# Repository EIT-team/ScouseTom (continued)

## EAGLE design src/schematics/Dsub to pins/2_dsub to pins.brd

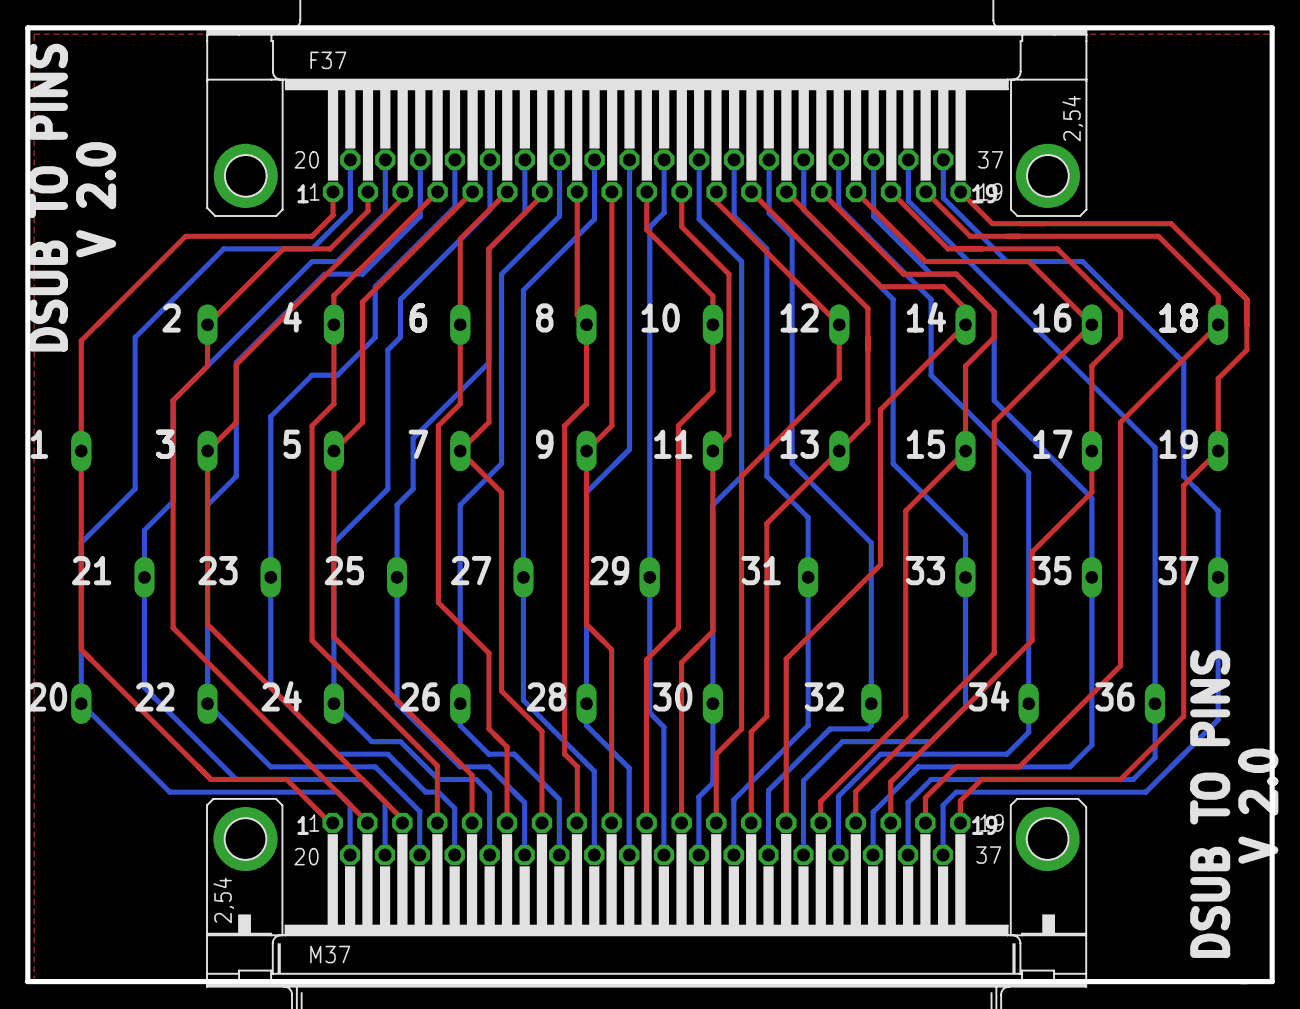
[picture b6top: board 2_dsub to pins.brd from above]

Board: 2 copper layers, 98.5 x 75.5 mm, 39 parts (0 on the bottom side), 37 nets.

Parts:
X1, X2, X3, X4, X5, X6, X7, X8, X9, X10, X11, X12, X13, X14, X15, X16, X17, X18, X19, X20, X21, X22, X23, X24, X25, X26, X27, X28, X29, X30, X31, X32, X33, X34, X35, X36, X37: 22-23-2021
X40: M37HP
X41: F37HP

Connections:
1: X1.1, X40.1, X41.1
2: X2.1, X40.2, X41.2
3: X3.1, X40.3, X41.3
4: X4.1, X40.4, X41.4
5: X5.1, X40.5, X41.5
6: X6.1, X40.6, X41.6
7: X7.1, X40.7, X41.7
8: X8.1, X40.8, X41.8
9: X9.1, X40.9, X41.9
10: X10.1, X40.10, X41.10
11: X11.1, X40.11, X41.11
12: X12.1, X40.12, X41.12
13: X13.1, X40.13, X41.13
14: X14.1, X40.14, X41.14
15: X15.1, X40.15, X41.15
16: X16.1, X40.16, X41.16
17: X17.1, X40.17, X41.17
18: X18.1, X40.18, X41.18
19: X19.1, X40.19, X41.19
20: X20.1, X40.20, X41.20
21: X21.1, X40.21, X41.21
22: X22.1, X40.22, X41.22
23: X23.1, X40.23, X41.23
24: X24.1, X40.24, X41.24
25: X25.1, X40.25, X41.25
26: X26.1, X40.26, X41.26
27: X27.1, X40.27, X41.27
28: X28.1, X40.28, X41.28
29: X29.1, X40.29, X41.29
30: X30.1, X40.30, X41.30
31: X31.1, X40.31, X41.31
32: X32.1, X40.32, X41.32
33: X33.1, X40.33, X41.33
34: X34.1, X40.34, X41.34
35: X35.1, X40.35, X41.35
36: X36.1, X40.36, X41.36
37: X37.1, X40.37, X41.37

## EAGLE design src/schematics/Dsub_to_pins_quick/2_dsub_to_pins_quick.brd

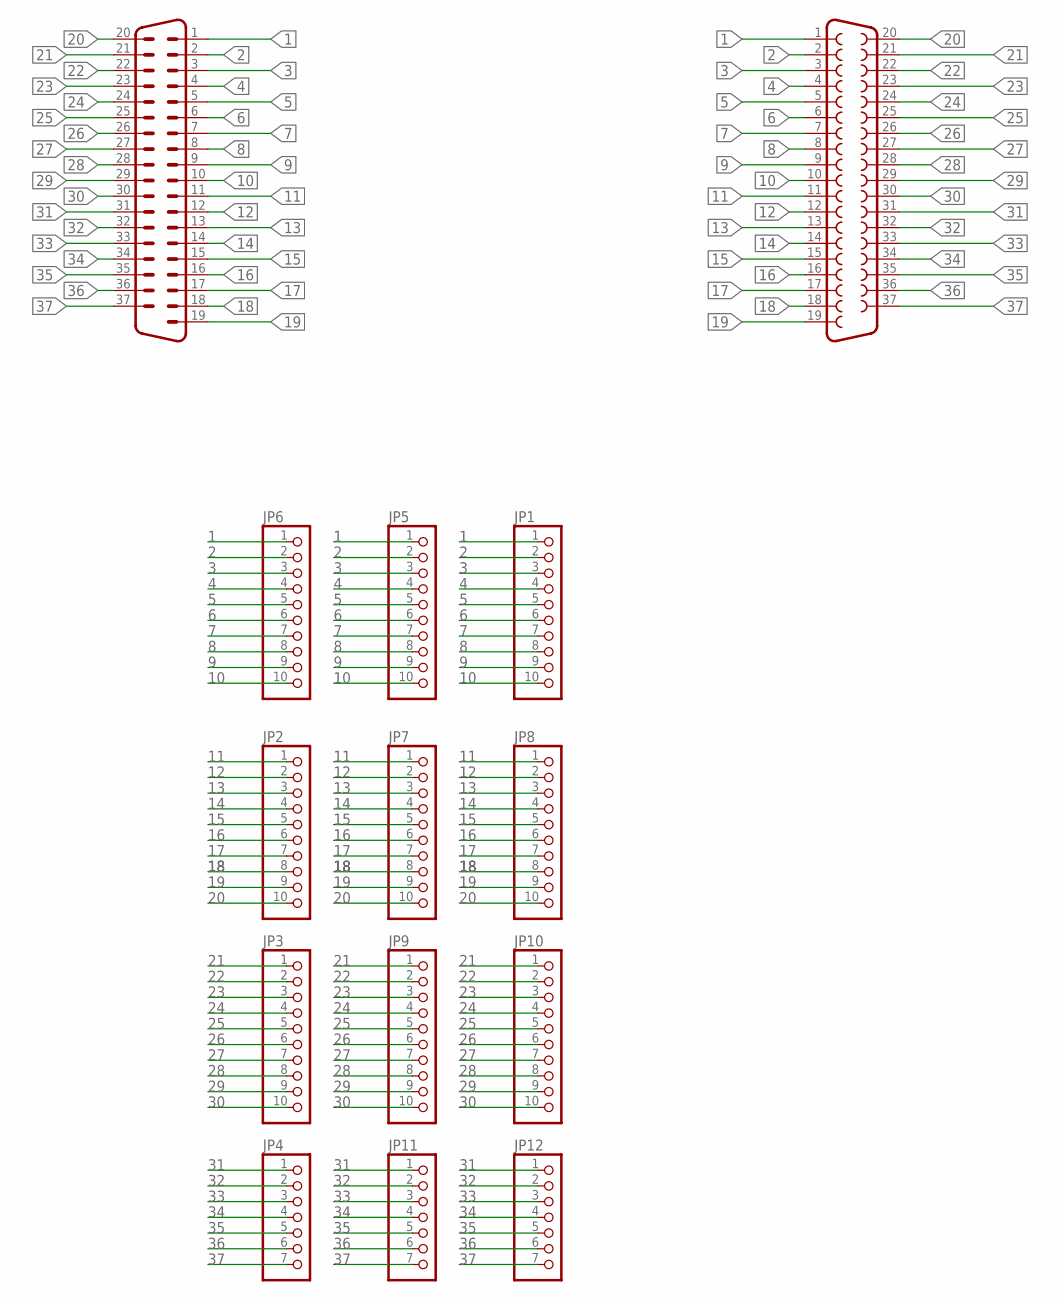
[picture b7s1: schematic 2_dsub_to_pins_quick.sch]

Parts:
JP1, JP2, JP3, JP5, JP6, JP7, JP8, JP9, JP10: PINHD-1X10; 1X10
JP4, JP11, JP12: PINHD-1X7; 1X07
X33: M37HP
X34: F37HP

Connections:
1: JP1.1, JP5.1, JP6.1, X33.1, X34.1
2: JP1.2, JP5.2, JP6.2, X33.2, X34.2
3: JP1.3, JP5.3, JP6.3, X33.3, X34.3
4: JP1.4, JP5.4, JP6.4, X33.4, X34.4
5: JP1.5, JP5.5, JP6.5, X33.5, X34.5
6: JP1.6, JP5.6, JP6.6, X33.6, X34.6
7: JP1.7, JP5.7, JP6.7, X33.7, X34.7
8: JP1.8, JP5.8, JP6.8, X33.8, X34.8
9: JP1.9, JP5.9, JP6.9, X33.9, X34.9
10: JP1.10, JP5.10, JP6.10, X33.10, X34.10
11: JP2.1, JP7.1, JP8.1, X33.11, X34.11
12: JP2.2, JP7.2, JP8.2, X33.12, X34.12
13: JP2.3, JP7.3, JP8.3, X33.13, X34.13
14: JP2.4, JP7.4, JP8.4, X33.14, X34.14
15: JP2.5, JP7.5, JP8.5, X33.15, X34.15
16: JP2.6, JP7.6, JP8.6, X33.16, X34.16
17: JP2.7, JP7.7, JP8.7, X33.17, X34.17
18: JP2.8, JP7.8, JP8.8, X33.18, X34.18
19: JP2.9, JP7.9, JP8.9, X33.19, X34.19
20: JP2.10, JP7.10, JP8.10, X33.20, X34.20
21: JP3.1, JP9.1, JP10.1, X33.21, X34.21
22: JP3.2, JP9.2, JP10.2, X33.22, X34.22
23: JP3.3, JP9.3, JP10.3, X33.23, X34.23
24: JP3.4, JP9.4, JP10.4, X33.24, X34.24
25: JP3.5, JP9.5, JP10.5, X33.25, X34.25
26: JP3.6, JP9.6, JP10.6, X33.26, X34.26
27: JP3.7, JP9.7, JP10.7, X33.27, X34.27
28: JP3.8, JP9.8, JP10.8, X33.28, X34.28
29: JP3.9, JP9.9, JP10.9, X33.29, X34.29
30: JP3.10, JP9.10, JP10.10, X33.30, X34.30
31: JP4.1, JP11.1, JP12.1, X33.31, X34.31
32: JP4.2, JP11.2, JP12.2, X33.32, X34.32
33: JP4.3, JP11.3, JP12.3, X33.33, X34.33
34: JP4.4, JP11.4, JP12.4, X33.34, X34.34
35: JP4.5, JP11.5, JP12.5, X33.35, X34.35
36: JP4.6, JP11.6, JP12.6, X33.36, X34.36
37: JP4.7, JP11.7, JP12.7, X33.37, X34.37

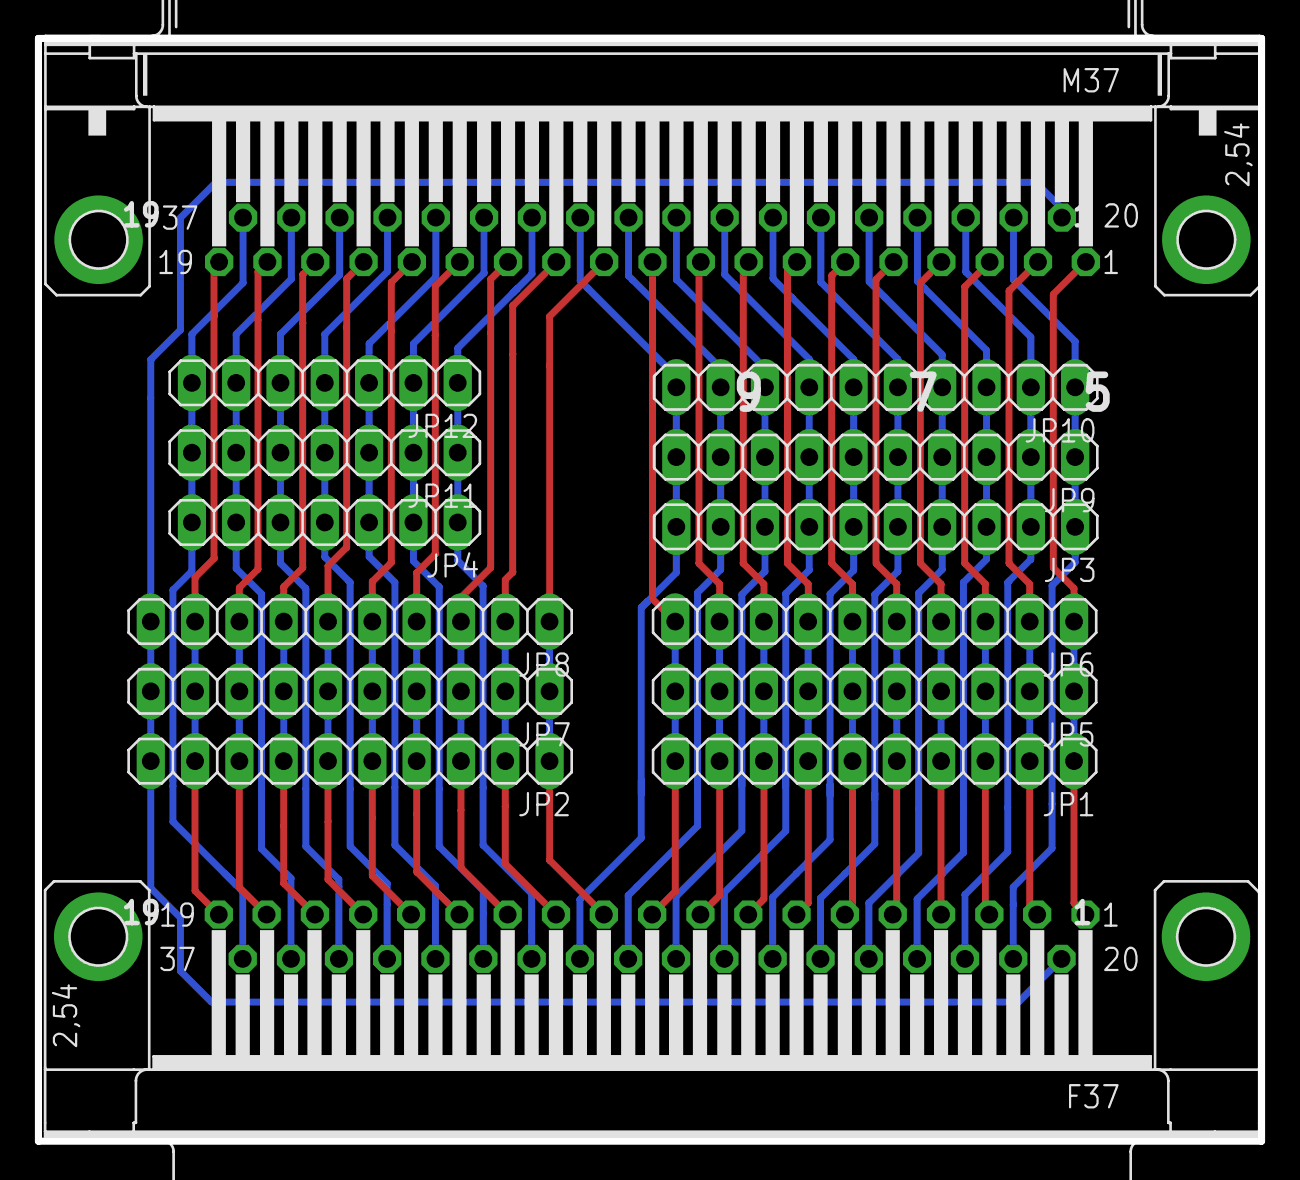
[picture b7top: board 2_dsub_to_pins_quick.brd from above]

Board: 2 copper layers, 70.1 x 63.2 mm, 14 parts (0 on the bottom side), 37 nets.

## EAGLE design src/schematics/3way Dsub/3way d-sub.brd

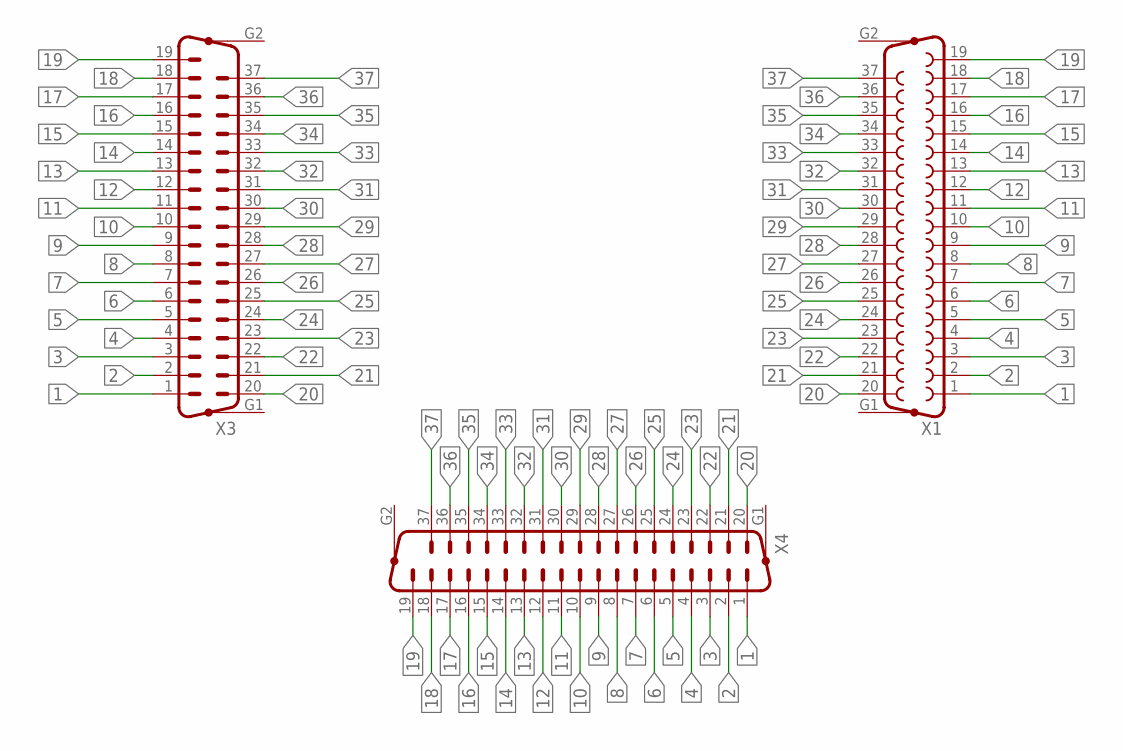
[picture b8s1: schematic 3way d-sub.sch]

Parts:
X1: F37HP
X3, X4: M37HP

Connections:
1: X1.1, X3.1, X4.1
2: X1.2, X3.2, X4.2
3: X1.3, X3.3, X4.3
4: X1.4, X3.4, X4.4
5: X1.5, X3.5, X4.5
6: X1.6, X3.6, X4.6
7: X1.7, X3.7, X4.7
8: X1.8, X3.8, X4.8
9: X1.9, X3.9, X4.9
10: X1.10, X3.10, X4.10
11: X1.11, X3.11, X4.11
12: X1.12, X3.12, X4.12
13: X1.13, X3.13, X4.13
14: X1.14, X3.14, X4.14
15: X1.15, X3.15, X4.15
16: X1.16, X3.16, X4.16
17: X1.17, X3.17, X4.17
18: X1.18, X3.18, X4.18
19: X1.19, X3.19, X4.19
20: X1.20, X3.20, X4.20
21: X1.21, X3.21, X4.21
22: X1.22, X3.22, X4.22
23: X1.23, X3.23, X4.23
24: X1.24, X3.24, X4.24
25: X1.25, X3.25, X4.25
26: X1.26, X3.26, X4.26
27: X1.27, X3.27, X4.27
28: X1.28, X3.28, X4.28
29: X1.29, X3.29, X4.29
30: X1.30, X3.30, X4.30
31: X1.31, X3.31, X4.31
32: X1.32, X3.32, X4.32
33: X1.33, X3.33, X4.33
34: X1.34, X3.34, X4.34
35: X1.35, X3.35, X4.35
36: X1.36, X3.36, X4.36
37: X1.37, X3.37, X4.37

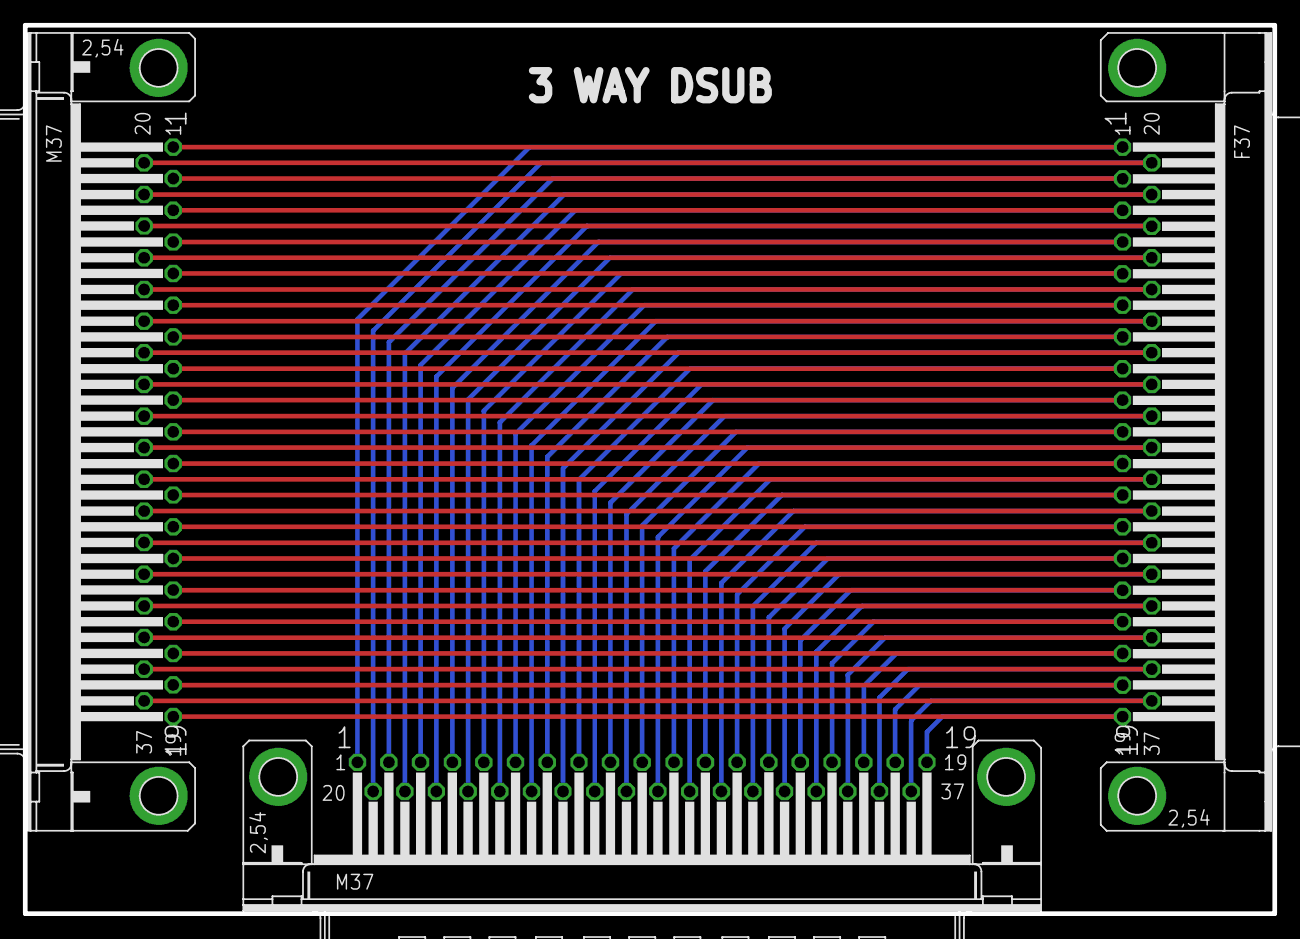
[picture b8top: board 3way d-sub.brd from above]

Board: 2 copper layers, 109.0 x 77.5 mm, 3 parts (0 on the bottom side), 37 nets.

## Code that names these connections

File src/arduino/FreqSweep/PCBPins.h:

/*Pin Numbering for PCB version - changed to reduce trace length */

// switch network pin definitions
const int DINp = 39;
const int DINn = 41;
const int SCLK = 43;
const int SYNC = 35;
const int RESET = 37;
const int TEST_1 = 33;
const int TEST_2 = 45;

// indicator pins
const int IND_SWITCH = 3;
const int IND_STIM = 4;
const int IND_START = 5;
const int IND_STOP = 6;
const int IND_FREQ = 9;

const int IND_EX_1 = 10;
const int IND_EX_2 = 11;
const int IND_EX_3 = 12;

//pins to turn the triggers on and off
const int TRIG_DISABLE_1 = 7;
const int TRIG_DISABLE_2 = 13;

//interupt pins
const int INTR_PMARK = 25; // pin to decect pmark - MUST BE AT POSITION 0 OF A DUE PORT 25 is 0 on portD - check http://arduino.cc/en/Hacking/PinMappingSAM3X
const int CS_EXTRA = 24; // bonus output pin on the CS side, not really used but whatever

//bonus pins
const int BONUS_1 = 47;
const int BONUS_2 = 49;
const int BONUS_3 = 51;
const int BONUS_4 = 53;

//Power Pins
const int PWR_STIM = 52;

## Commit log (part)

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2015-04-14 Added most of the old software and hardware, with very brief readmes. All in a state that would only make sense to current users.
    Also added new Controller software - latest version which has been used by kirill and jimmy so far - more testing needed
2015-04-14 changed fig
    bylad
2015-04-24 First Injection Bug Fixed
    Bug where the channels were not opened for the first injection after the
    switch board was turned on. Cause was incorrect timing of the reset and
    sync pins, so the switches were not in a receptive state until the
    second injection.
    Also, added delay to start of injection as CS takes ~50ms to actually
    start injecting. Trigger channels now correspond to when the current
2015-05-08 removed spaces in fig names
2015-05-08 tried raw git for svg
2015-05-12 If this is a previous version of ScouseTom, but it's deprecated, it should not be in the latest version of the active most updated branch.
2015-05-12 Move MatLab stuff from ScouseTom/ArduinoControl/Control to ScouseTom/src/matlab. Also, mat files are in resources/data, and txt files are in config/matlab.
2015-05-12 Tests in Test_Arduino_Controller, minus the vcxproj, sln, suo files
2015-05-12 Arduino code from ScouseTom_Control and Stimulation_Calibration
2015-05-12 All files Arduino Controller moved to new folder structure.
2015-05-12 Corrected typo in resources folder name
2015-05-12 Added pulsing at start to check for errors on start up
2015-05-15 Started Case Design. Changed PCB pin PWR_SWTICH as used in serial1 on Due
2015-05-18 Completed ScouseTom Case Design in SW2015. Reference Arduino Due modifyed from one on GrabCad. Stl included for printing
2015-05-18 Updated Case Design so that it actually fits...
2015-05-18 rearranged ExpSetup so all non essential variables are stored in Info struct. This is updated each time SendSettings used. Prevented Millions of Testing.logs being made
2015-05-27 Updated Case to provide extra room for cables and 37way DSUB on to for Biosemi
2015-05-29 Tom's Switch Network Design Files
2015-05-29 Create DDS_Code_Arduino.o
    This is the code to program the Parallel Current Source via SPI.
2015-06-01 Create headers for all *.ino files because it's needed by PlatformIO. Also, tidying up consts.
2015-06-19 Moved Toms Schematics all into doc/schematics
2015-06-23 moved schematics from Doc to Source
2015-07-01 gerber files and ignoring eagle backups
2015-07-01 fixed gitignore for eagle auotsaves
2015-07-01 editing gitignore again agin
2015-07-01 more messing with gitignore
2015-07-02 Testing GitHub for Windows
2015-07-07 Added Mak Connector for Silicon Elec to Schematics. Started routing Switchboard
2015-07-09 SwitchBoard Switches routed
2015-07-20 SwitchNetwork Finished. Gerber/BOM/P&P generated
2015-07-21 Measurement Time per frequency added, should still be compatible with previous versions. User can either set time by certain number of periods of sine wave (with offset) or by milliseconds directly
2015-07-22 Put ALL consts into relevant .h files
2015-07-22 Added Bad Electrode Function - User can specify electrodes to ignore in protocol and current injection
2015-07-24 Changed ExpSetup so user specifies target stim voltage only. Minor bug fixes
2015-07-24 Fixed Clock speed of indicator (wrong TIMER setting) and added pulses for stimulator channel
2015-07-27 Stopped Halt being run when system is idle. This stops extra stop triggers at the end of the injection
2015-07-28 changed delay on stimulation ID pulse
2015-07-28 un messed with readme to test sourcetree
2015-07-28 Started Debug Phantom with Dsub Connection
2015-07-31 IM A FUCKING IDIOT! Forgot to transfer the code from laptop which included the changes necessary to work with the AD isolator
2015-08-04 debug phantom before routing
2015-08-05 Added 3ms delay before start of Multi Inject, as the Start Trigger was occuring so close to the inital ID pulses that it was confusing the processing code
2015-08-19 minor changes to switchnetwork gerber
2015-08-20 Configure PlatformIO to run with own libraries and customised source folders.
2015-08-20 Moved to arduino lib folder.
2015-08-20 started iso test
2015-08-20 Function declarations changes since platformio doesn't like comments right after function headers.
2015-08-20 Visual Micro files are not needed anymore.
2015-08-20 Added Switch Iso test
2015-08-20 Updated test for new switch network - It works
2015-08-21 minor schematic change i think from opening and closing
2015-08-26 Started Moving things to Libary folder, was all ok until ran into problems with multiple definitions. Will come back to this later!
2015-08-27 Added Complicance Check Test. Changed the PWR test to refer to ONLY stimulation
2015-08-28 Added command to Matlab to check switches, minor changes to text ouputs in validatesettings
2015-09-01 Update Compliance Test with function to set compliance in function
2015-09-01 Added Check Compliance functions to ScouseTom_Control. Made Trig Check function not shit
2015-09-03 Added Compliance Status Check to SingleFreqInjection Mode. Checks halfway through injection time. Status of each protocol line sent to PC each repetition. Need to add decoding this to Matlab code
2015-09-04 example of how doxygen works in arduino
2015-09-08 convert comments to doxygen style; slightly improve coding style.
2015-09-08 change comments to doxygen style of BreadboardPins.h, CS_comm, Compliance, Injection, PC_comm
2015-09-15 Finihsed compliance check in main injection and separate check
2015-09-15 Added Double Pulse for complete protocol
2015-09-17 Finished Initial Version of New Case Design
2015-09-21 Finished Shield Case Design. Added Model of SwitchBoard
2015-09-22 Finished SwitchBoard Case and Lid
2015-09-23 updated switchboard with proper daisy chain select and test 1 correct wiring
2015-09-25 Added Dsub Cover Final, Fixed bug in Contact Check Compliance - Now references the *contact check* rprotocol in calc
2015-09-29 Changed the multifrequency mode to not have to stop and start before each freq change. This required calculation of the output range of the CS, and then turning off both methods of automatically sett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
2015-09-30 added extra pulse to freqchange so processing is easier
2015-10-13 fixed IEC60601 check
2015-10-20 Revert "Each arduino folder needs its own platformio.ini"
    This reverts commit b0bcd410d381563033a3b09cfbd3fae94a5f1aef.
2015-11-02 Updated the CS communication so the timeout could be specified and returns false if it timed out. Thus the compliance timeout limit can be shorted to not disrupt short injections
2015-11-02 User now specifies Compliance in ExpSetup. Adjusted SendSettings & GetExpSetup Accordingly. Made Matlab code m uch less verbose. Changed how stim timings are compared to measurement time as bug arose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
2015-11-02 Less verbose init
2015-11-03 Added prompt for user to start contact check
2015-11-03 Added Compliance Check to MultiFreq, reports bad if a single freq is bad
2015-11-05 Corrected part no for Micro USB on switch network
2015-12-07 Changed the timing on the check triggers function so it can be visible on default biosmi settings
2016-01-05 Improved rounding of output from current source, to fix bug in issue #41@
2016-01-07 Added Platformio Project file To Switch_Iso_test
2016-01-07 Made text clearer in Switch Test, changed number of boards to 3
2016-01-07 removed visual micro folder
2016-01-07 Mayo helped squash a bug. Daisy CHain works!
2016-01-07 Moved Serial Begin to *after* first CS_init to ensure correct order of info sent during Ard_init
2016-01-25 minor layout changes
2016-01-25 Changed All Front Panel Messages to Variables
2016-01-25 Added check for *which* error type was sent by arduino, so only critical errors make system stop. Timeout codes (which are most likely) do not stop system now
2016-01-25 More useful errors at start of contact check and added try/catch statements
2016-02-04 Changed ValidateExpSetup to pause on warning msgbox
2016-02-16 Added Sequential trigger test for debugging actichamp triggers
2016-02-17 Added dummy pulses on extra chn in place of falling edge
2016-02-22 Fiddling with ActiChampTriggers - using dummy channel to force recognition of falling edge
2016-02-22 Save srnshot to same folder as bdf and get focus on biosemi window@
2016-02-22 Added Compliance code to starting triggers
2016-02-22 Added New Trigger Stuff To ScouseTom Control
2016-03-01 Updated ScouseTom Shield SilkScreen and Gerber for PCB train order
2016-03-01 Minor Silkscreen updates to SwitchBoard. New Gerber files and updated BOM and P&P with lipo connector
2016-03-01 Files ready to send to PCBTrain
2016-03-02 added Due Pinout AS I STILL GET THIS WRONG
2016-03-04 Added calculation of number of parts needed to order. I hate excel
2016-03-14 updated Farnell order spreadsheet
2016-03-14 Removed refs to PWR_SWITCH, which is no longer used
2016-03-22 added profiler saving to debugmode
2016-04-01 removed profiling things from scousetomstart
2016-04-05 removed obsolete header file
2016-04-07 added firmware docs for firmware upgrade with instructions
2016-04-22 Added test to contiouously loop through a protocol
2016-04-26 fixed imortality reached message
2016-05-13 added mak gerber files
2016-05-18 minor
2016-05-18 Added FreqSweep Code
2016-05-18 check the tag for stim
2016-05-18 added more init
2016-05-20 Updated stim calc phase delay, so it rounds up to nearest int, and sends correct data over serial
2016-05-20 some software updates for processing
    blah
2016-06-09 from upstairs
    pulse bipolar
2016-08-02 minor stuff
    minor changes for stevenage
2016-08-24 uncommited changes on toshiba laptop
2016-09-02 added simple matlab communication to CS
2016-09-05 Added text to warn you are using nanogit add -Agit add -A
2016-09-28 muxes can be set through serial port
2016-09-29 Added turning on and off muxes
2016-11-08 Resistor Phantom v1
2017-01-03 minor updates to make overview figure nicer
2017-01-09 Added LTSpice model
2017-01-30 started SPICE model for OuputZ tester
2017-02-07 Example Spice models for Impedance testers
2017-02-07 Added more documentation to readmes in each folder
2017-02-08 Fixed broken link in readme
2017-02-20 Finished sim of TIA and Droop circuit. Started PCB
2017-02-21 one mo' 'gin
2017-02-21 Finished layout and SS. Added gerbers
2017-02-23 The spice is life
2017-02-24 added OPA2188 sim and lib file
2017-02-27 Added First go at Dsub2Croc connector case
2017-03-06 fixed bug in range settings for >250 nA
2017-03-08 Added OPA2188 to spice lib. fiddling with Monte Carlo sim
2017-03-08 fixed ref to old pins
2017-05-03 removed starting id codes on stim trigger line
2017-05-03 rename stuff
2017-05-23 Sped up sending waveform to CS for multiple start recordings
2017-05-25 added multi plot and single files to start
2017-07-04 Changes made by Mayo and things
2017-07-13 cahnges to Crab stuff
2017-08-01 more typos fixed
2017-08-08 changes for simple stim with 1 keithley
2017-08-10 Fixed bug in stim output
2017-08-10 testing - corrected for jitter in scope data
2017-08-10 improved phase calc
2017-08-11 Added simple test of jitter on pin interrupt
2017-08-14 added more changes to try and pin down jitter
2017-08-17 checking stimulation timings and phase delays
2017-09-06 made stim keithley monophasic
2017-09-06 changed baud rate
2017-09-21 Added New Dsub connector. Updated Dsub2pins
2017-09-22 Board for laser cut electrodes
2017-11-23 Dsub box, fixed trace on debug phantom. Gerber and CAM data for pcbway
2018-01-08 stim seq
2018-01-09 Stim sequence working, with flag to use normal stim settings
2018-01-30 removed .epf files as they get saved just from opening designs. annoying
2018-01-31 Added pulldown resistors on CS and Switch board comm
2018-02-08 Gerbers for updated shield, sent to PCBtrain. Minor edits to routing
2018-03-28 changed so keithley display shows nano
2018-04-04 working with 4 electrodes and converted to nano
2018-04-04 changed message to make obvious in 4 shunted branch
2018-04-12 added samtec library
2018-04-20 forced matlab to assume 2 boards on startup
2018-05-23 making new branch for the new randomized summation subtraction!
2018-09-13 weird old changes
    check it does not screw things up
2018-09-13 CS now waights for the trifgger in channel 4
2018-09-16 external triggering from line 2 working
2018-09-16 4 shunt nano with external triggering
2018-09-18 some updates
2018-10-08 Anna's computer
    Working code on the hospital machine from Anna's computer
2018-10-17 new start files for stim vs no stim and got ride of current warining in validate expsetup
2018-12-18 changed resistor values in schematic
2019-02-04 Made rotations of capactiors clearer on silkscreen
2019-02-12 option to not stim
2019-02-12 working start files
